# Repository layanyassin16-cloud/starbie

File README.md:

HELLOOOOO and welcome to my first ever readme where I yap because I have absolutely no idea what I'm doing. ok so basically this is a starbie starter project it's like a virtual desktop pet
kinda like a tamagotchi and there's two buttons and yeah!!! I did it to learn about PCB boards and drawing schematics and stuff.

that's my PCB board!!! it took me some time to figure out how to route everything but its actually not too hard once you know what you're doing
here are the controls:
-----Button 1, first press- opens the radial menu
----- if you tilt while the menu is open- moves the selector ball
-----button 1, second press- selects the highlighted action
-----button 2- you can show/ hide the stats screen
-----shake when you can see the pet- animation

my schematic 
the microcotnroaoller looks weird bc my computer wouldn't let me download it (i'm using the web browser version) and I had to manually create it

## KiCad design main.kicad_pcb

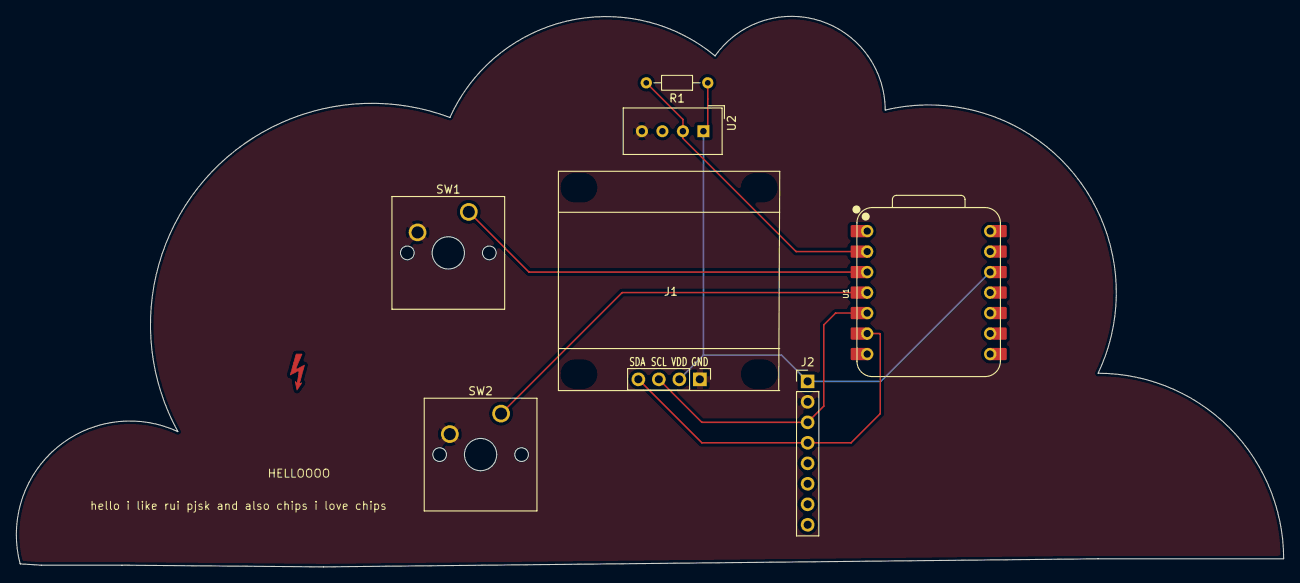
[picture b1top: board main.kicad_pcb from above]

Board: 2 copper layers, 157.1 x 68.2 mm, 7 parts (0 on the bottom side), 7 nets.

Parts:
J1: Conn_01x04_Pin; Display_128x64_096_I2C
J2: Conn_01x08_Pin; PinHeader_1x08_P2.54mm_Vertical
R1: 10k; R_Axial_DIN0204_L3.6mm_D1.6mm_P7.62mm_Horizontal
SW1, SW2: SW_Push; SW_Cherry_MX_1.00u_PCB
U1: XIAO-ESP32-C6-DIP
U2: DHT11; Aosong_DHT11_5.5x12.0_P2.54mm

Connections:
+3.3V: J1.2, J2.1, R1.1, U1.12 (3V3_OUT), U2.1 (VDD)
/DHT11 DATA: R1.2, U1.2 (D1), U2.2 (DATA)
/GP102: SW1.1, U1.3 (D2)
/GP103: SW2.1, U1.4 (D3)
/SCL: J1.3, J2.3, U1.5 (D4)
/SDA: J1.4, J2.4, U1.6 (D5)
GND: J1.1, J2.2, SW1.2, SW2.2, U2.4 (GND)
